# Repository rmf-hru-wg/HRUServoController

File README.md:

UEC RMF HRU Servo Controller Board RP2040
===

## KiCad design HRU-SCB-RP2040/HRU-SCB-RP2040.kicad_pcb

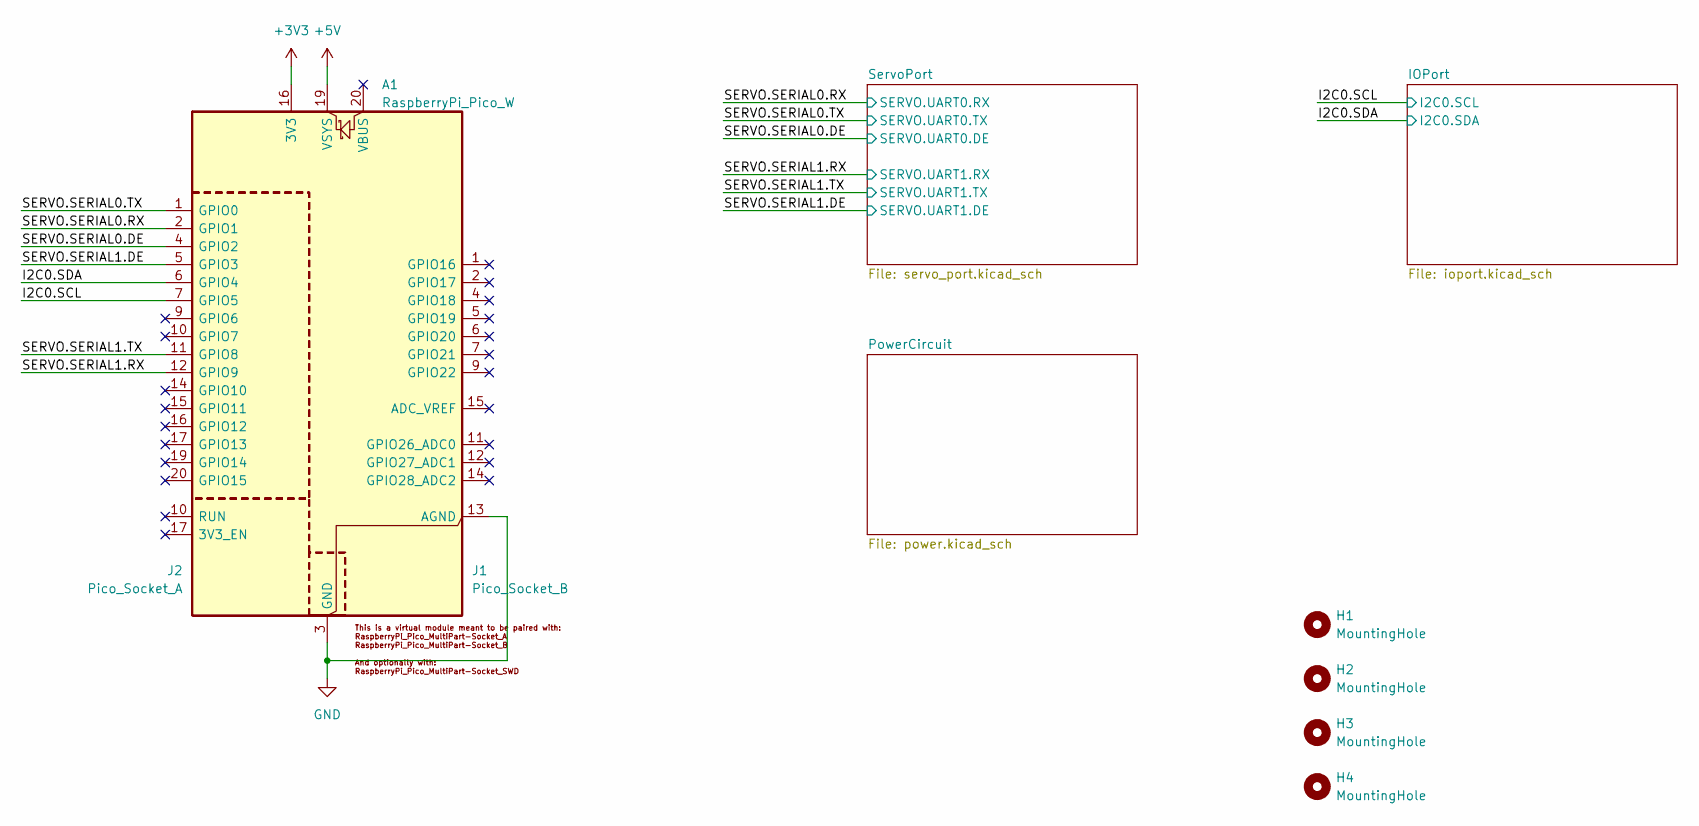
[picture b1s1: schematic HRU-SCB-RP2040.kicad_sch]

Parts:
A1: RaspberryPi_Pico_W; RaspberryPi_Pico_W_Virtual
H1, H2, H3, H4: MountingHole; MountingHole_3.2mm_M3
J1: Pico_Socket_B; RaspberryPi_Pico_PinSocket_1x20_P2.54mm_Vertical
J2: Pico_Socket_A; RaspberryPi_Pico_PinSocket_1x20_P2.54mm_Vertical

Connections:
+3V3: J1.16 (3V3); also elsewhere on the board
+5V: J1.19 (VSYS); also elsewhere on the board
/I2C0.SCL: J2.7 (GPIO5); also elsewhere on the board
/I2C0.SDA: J2.6 (GPIO4); also elsewhere on the board
/SERVO.SERIAL0.DE: J2.4 (GPIO2); also elsewhere on the board
/SERVO.SERIAL0.RX: J2.2 (GPIO1); also elsewhere on the board
/SERVO.SERIAL0.TX: J2.1 (GPIO0); also elsewhere on the board
/SERVO.SERIAL1.DE: J2.5 (GPIO3); also elsewhere on the board
/SERVO.SERIAL1.RX: J2.12 (GPIO9); also elsewhere on the board
/SERVO.SERIAL1.TX: J2.11 (GPIO8); also elsewhere on the board
GND: J1.3 (GND), J1.8 (GND), J1.13 (AGND), J1.18 (GND), J2.3 (GND), J2.8 (GND), J2.13 (GND), J2.18 (GND); also elsewhere on the board

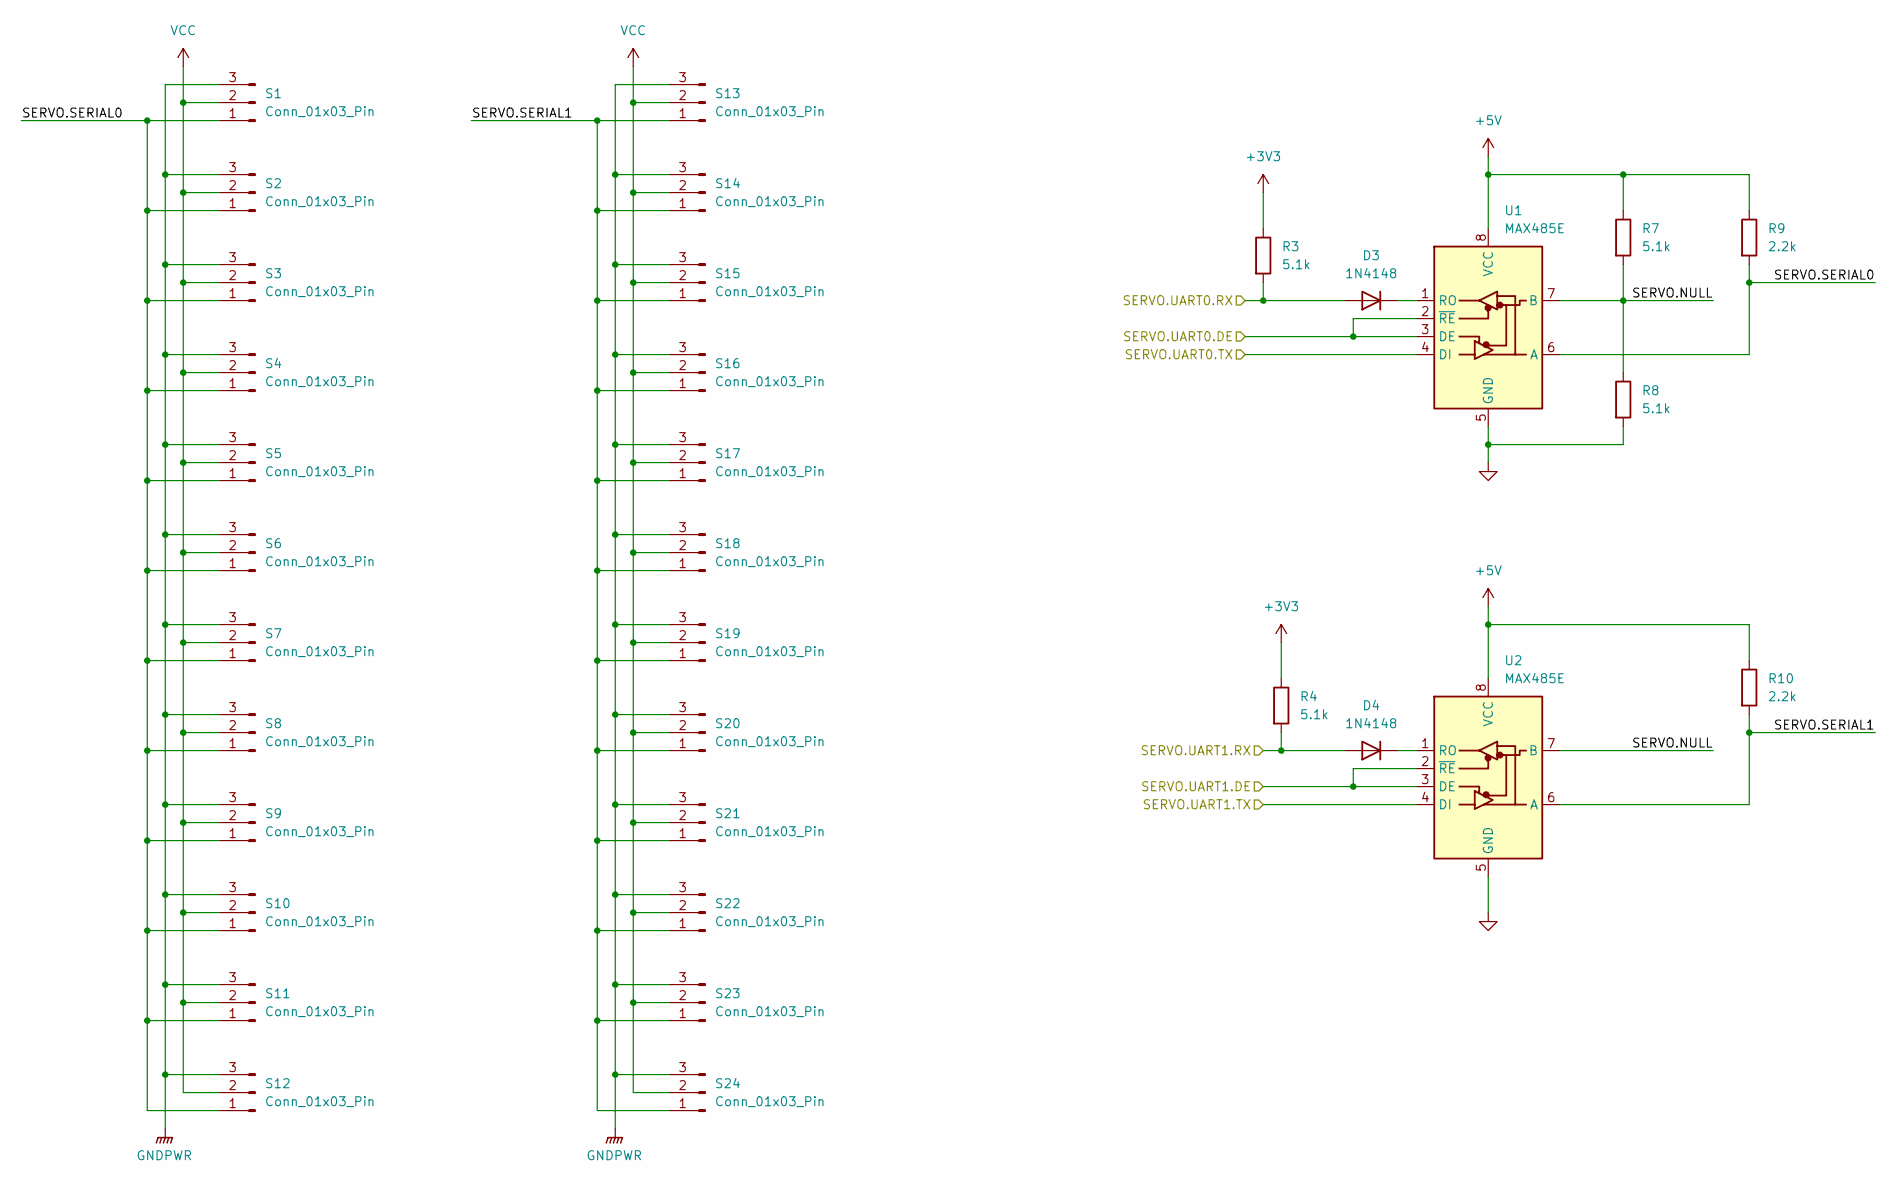
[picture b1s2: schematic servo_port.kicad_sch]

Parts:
D3, D4: 1N4148; D_T-1_P5.08mm_Horizontal
R3, R4, R7, R8: 5.1k; R_Axial_DIN0207_L6.3mm_D2.5mm_P7.62mm_Horizontal
R9, R10: 2.2k; R_Axial_DIN0207_L6.3mm_D2.5mm_P7.62mm_Horizontal
S1, S2, S3, S4, S5, S6, S7, S8, S9, S10, S11, S12, S13, S14, S15, S16, S17, S18, S19, S20, S21, S22, S23, S24: Conn_01x03_Pin; PinHeader_1x03_P2.54mm_Vertical_SmallCourtyard
U1, U2: MAX485E; DIP-8_W7.62mm_Socket

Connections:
+3V3: R3.1, R4.1; also elsewhere on the board
+5V: R7.1, R9.1, R10.1, U1.8 (VCC), U2.8 (VCC); also elsewhere on the board
/SERVO.SERIAL0.DE: U1.2 (~RE), U1.3 (DE); also elsewhere on the board
/SERVO.SERIAL0.RX: D3.2 (A), R3.2; also elsewhere on the board
/SERVO.SERIAL0.TX: U1.4 (DI); also elsewhere on the board
/SERVO.SERIAL1.DE: U2.2 (~RE), U2.3 (DE); also elsewhere on the board
/SERVO.SERIAL1.RX: D4.2 (A), R4.2; also elsewhere on the board
/SERVO.SERIAL1.TX: U2.4 (DI); also elsewhere on the board
/ServoPort/SERVO.NULL: R7.2, R8.1, U1.7 (B), U2.7 (B)
/ServoPort/SERVO.SERIAL0: R9.2, S1.1, S2.1, S3.1, S4.1, S5.1, S6.1, S7.1, S8.1, S9.1, S10.1, S11.1, S12.1, U1.6 (A)
/ServoPort/SERVO.SERIAL1: R10.2, S13.1, S14.1, S15.1, S16.1, S17.1, S18.1, S19.1, S20.1, S21.1, S22.1, S23.1, S24.1, U2.6 (A)
GND: R8.2, U1.5 (GND), U2.5 (GND); also elsewhere on the board
GNDPWR: S1.3, S2.3, S3.3, S4.3, S5.3, S6.3, S7.3, S8.3, S9.3, S10.3, S11.3, S12.3, S13.3, S14.3, S15.3, S16.3, S17.3, S18.3, S19.3, S20.3, S21.3, S22.3, S23.3, S24.3; also elsewhere on the board
unnamed: D3.1 (K), U1.1 (RO)
unnamed: D4.1 (K), U2.1 (RO)
VCC: S1.2, S2.2, S3.2, S4.2, S5.2, S6.2, S7.2, S8.2, S9.2, S10.2, S11.2, S12.2, S13.2, S14.2, S15.2, S16.2, S17.2, S18.2, S19.2, S20.2, S21.2, S22.2, S23.2, S24.2; also elsewhere on the board

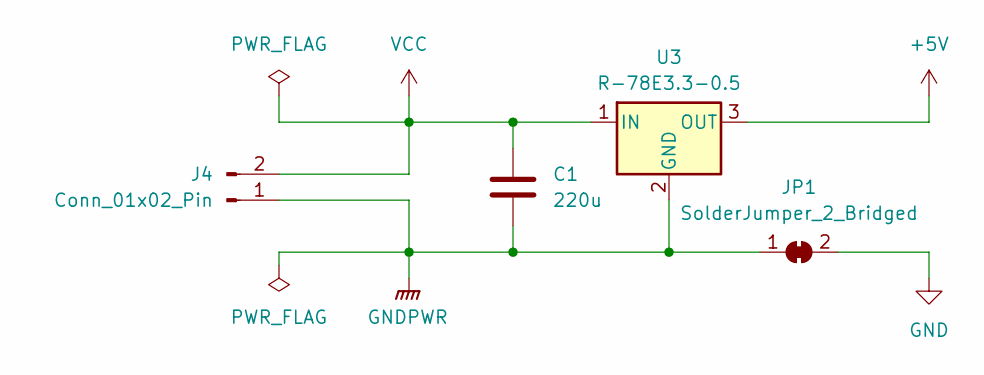
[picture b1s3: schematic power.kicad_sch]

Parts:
C1: 220u; C_Radial_D8.0mm_H11.5mm_P3.50mm
J4: Conn_01x02_Pin; AMASS_XT30UPB-M_1x02_P5.0mm_Vertical
JP1: SolderJumper_2_Bridged; SolderJumper-2_P1.3mm_Bridged_Pad1.0x1.5mm
U3: R-78E3.3-0.5; Converter_DCDC_RECOM_R-78E-0.5_THT

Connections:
+5V: U3.3 (OUT); also elsewhere on the board
GND: JP1.2 (B); also elsewhere on the board
GNDPWR: C1.2, J4.1, JP1.1 (A), U3.2 (GND); also elsewhere on the board
VCC: C1.1, J4.2, U3.1 (IN); also elsewhere on the board

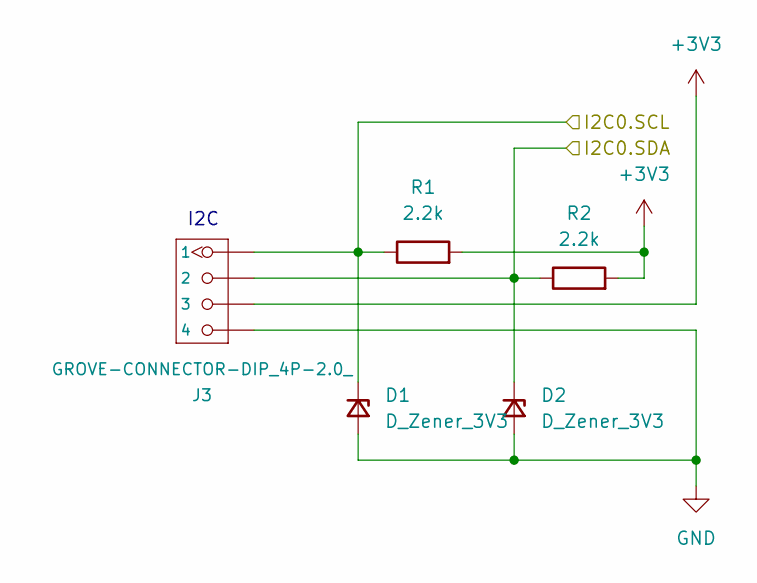
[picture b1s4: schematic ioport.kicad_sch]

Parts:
D1, D2: D_Zener_3V3; D_T-1_P5.08mm_Horizontal
J3: GROVE-CONNECTOR-DIP_4P-2.0_; GROVE-HW4-2.0
R1, R2: 2.2k; R_Axial_DIN0207_L6.3mm_D2.5mm_P7.62mm_Horizontal

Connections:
+3V3: J3.3, R1.2, R2.2; also elsewhere on the board
/I2C0.SCL: D1.1 (K), J3.1, R1.1; also elsewhere on the board
/I2C0.SDA: D2.1 (K), J3.2, R2.1; also elsewhere on the board
GND: D1.2 (A), D2.2 (A), J3.4; also elsewhere on the board

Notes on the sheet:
I2C

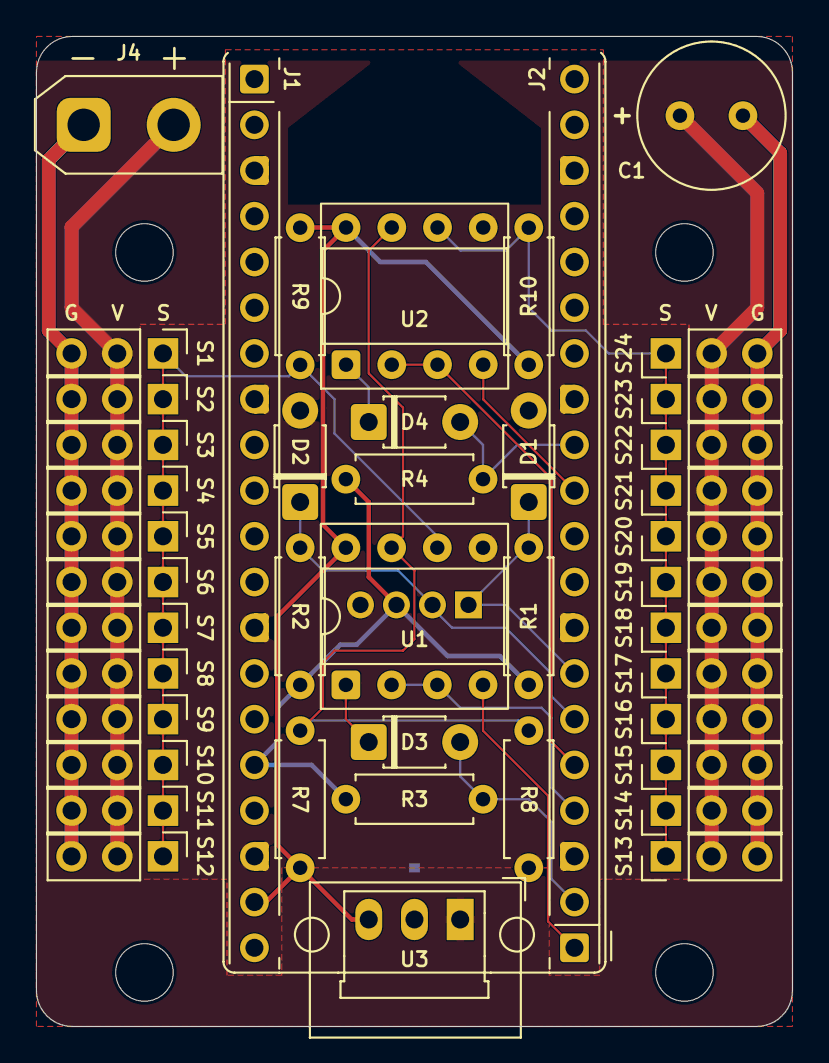
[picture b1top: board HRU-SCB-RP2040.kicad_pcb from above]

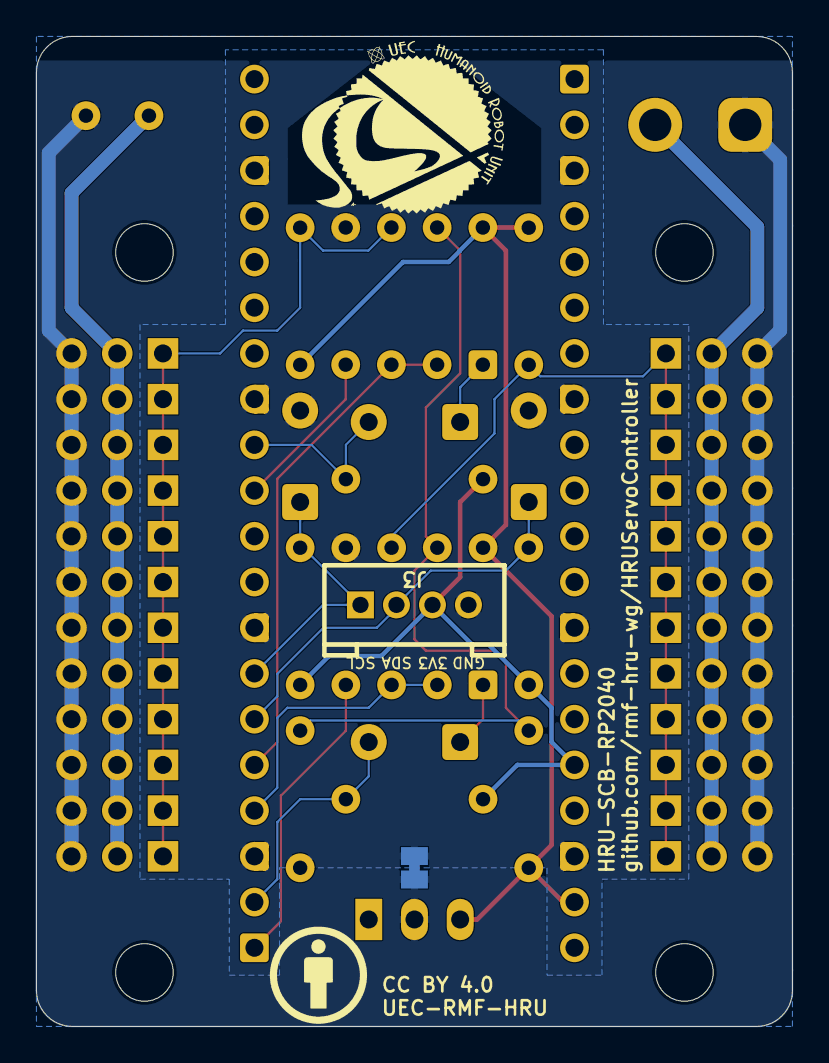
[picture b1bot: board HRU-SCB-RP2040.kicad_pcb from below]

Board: 2 copper layers, 42.0 x 55.0 mm, 50 parts (2 on the bottom side), 18 nets.

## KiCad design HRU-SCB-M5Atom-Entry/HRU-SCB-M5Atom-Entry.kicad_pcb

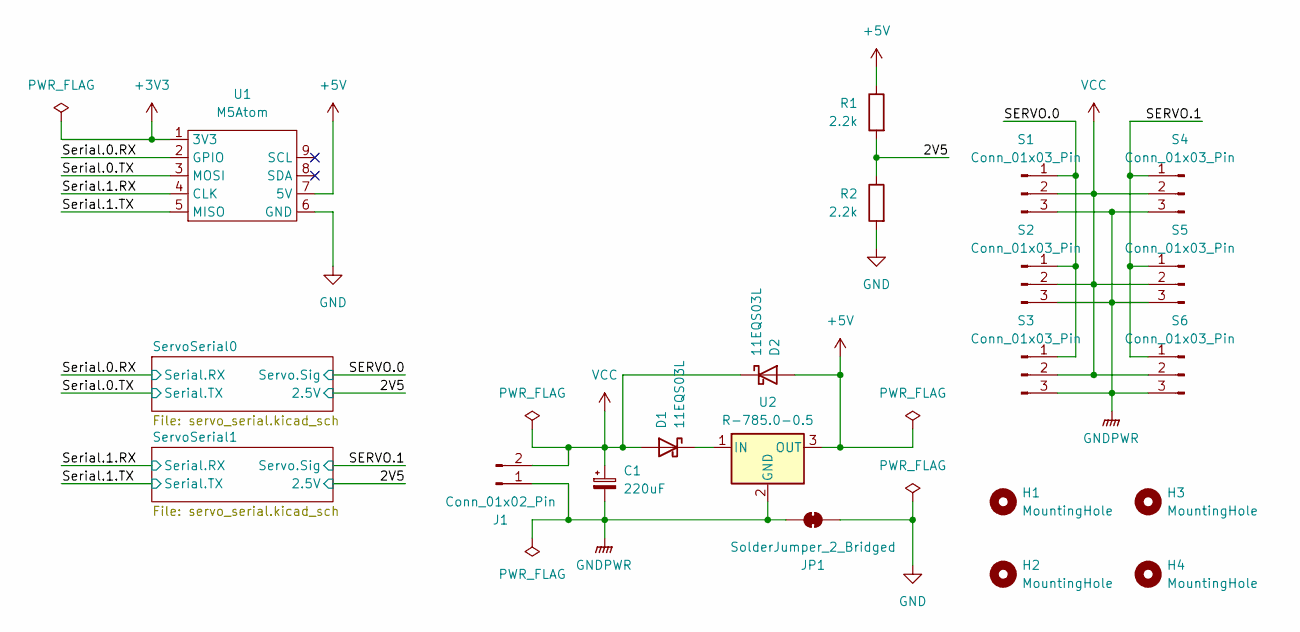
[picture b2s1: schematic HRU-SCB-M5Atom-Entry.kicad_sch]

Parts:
C1: 220uF; CP_Radial_D6.3mm_P2.50mm
D1, D2: 11EQS03L; D_T-1_P5.08mm_Horizontal
H1, H2, H3, H4: MountingHole; MountingHole_2.2mm_M2
J1: Conn_01x02_Pin; AMASS_XT30U-M_1x02_P5.0mm_Vertical
JP1: SolderJumper_2_Bridged; SolderJumper-2_P1.3mm_Bridged_Pad1.0x1.5mm
R1, R2: 2.2k; R_Axial_DIN0207_L6.3mm_D2.5mm_P7.62mm_Horizontal
S1, S2, S3, S4, S5, S6: Conn_01x03_Pin; PinHeader_1x03_P2.54mm_Vertical_SmallCourtyard
U1: M5Atom
U2: R-785.0-0.5; Converter_DCDC_RECOM_R-78E-0.5_THT

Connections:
+3V3: U1.1 (3V3); also elsewhere on the board
+5V: D2.2 (A), R1.1, U1.7 (5V), U2.3 (OUT); also elsewhere on the board
/2V5: R1.2, R2.1; also elsewhere on the board
/SERVO.0: S1.1, S2.1, S3.1; also elsewhere on the board
/SERVO.1: S4.1, S5.1, S6.1; also elsewhere on the board
/Serial.0.RX: U1.2 (GPIO); also elsewhere on the board
/Serial.0.TX: U1.3 (MOSI); also elsewhere on the board
/Serial.1.RX: U1.4 (CLK); also elsewhere on the board
/Serial.1.TX: U1.5 (MISO); also elsewhere on the board
GND: JP1.2 (B), R2.2, U1.6 (GND); also elsewhere on the board
GNDPWR: C1.2, J1.1, JP1.1 (A), S1.3, S2.3, S3.3, S4.3, S5.3, S6.3, U2.2 (GND)
unnamed: D1.1 (K), U2.1 (IN)
VCC: C1.1, D1.2 (A), D2.1 (K), J1.2, S1.2, S2.2, S3.2, S4.2, S5.2, S6.2

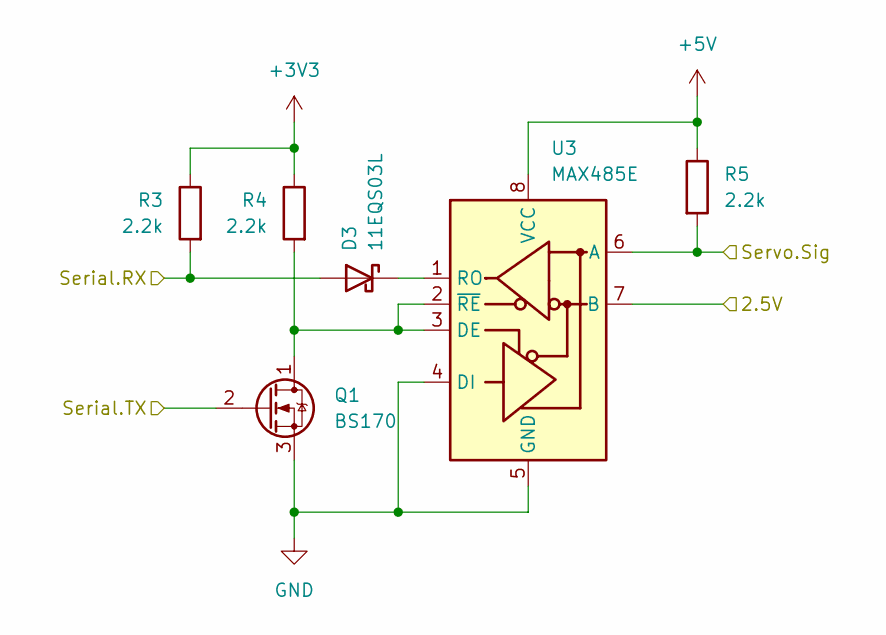
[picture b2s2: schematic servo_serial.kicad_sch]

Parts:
D3: 11EQS03L; D_T-1_P5.08mm_Horizontal
Q1: BS170; TO-92_Inline
R3, R4, R5: 2.2k; R_Axial_DIN0207_L6.3mm_D2.5mm_P7.62mm_Horizontal
U3: MAX485E; DIP-8_W7.62mm_Socket

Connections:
+3V3: R3.1, R4.1; also elsewhere on the board
+5V: R5.1, U3.8 (VCC); also elsewhere on the board
/2V5: U3.7 (B); also elsewhere on the board
/SERVO.0: R5.2, U3.6 (A); also elsewhere on the board
/Serial.0.RX: D3.2 (A), R3.2; also elsewhere on the board
/Serial.0.TX: Q1.2 (G); also elsewhere on the board
GND: Q1.3 (S), U3.4 (DI), U3.5 (GND); also elsewhere on the board
unnamed: D3.1 (K), U3.1 (RO)
unnamed: Q1.1 (D), R4.2, U3.2 (~RE), U3.3 (DE)

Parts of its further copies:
D4: 11EQS03L; D_T-1_P5.08mm_Horizontal
Q2: BS170; TO-92_Inline
R6, R7, R8: 2.2k; R_Axial_DIN0207_L6.3mm_D2.5mm_P7.62mm_Horizontal
U4: MAX485E; DIP-8_W7.62mm_Socket

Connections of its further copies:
+3V3: R6.1, R7.1; also elsewhere on the board
+5V: R8.1, U4.8 (VCC); also elsewhere on the board
/2V5: U4.7 (B); also elsewhere on the board
/SERVO.1: R8.2, U4.6 (A); also elsewhere on the board
/Serial.1.RX: D4.2 (A), R6.2; also elsewhere on the board
/Serial.1.TX: Q2.2 (G); also elsewhere on the board
GND: Q2.3 (S), U4.4 (DI), U4.5 (GND); also elsewhere on the board
unnamed: D4.1 (K), U4.1 (RO)
unnamed: Q2.1 (D), R7.2, U4.2 (~RE), U4.3 (DE)

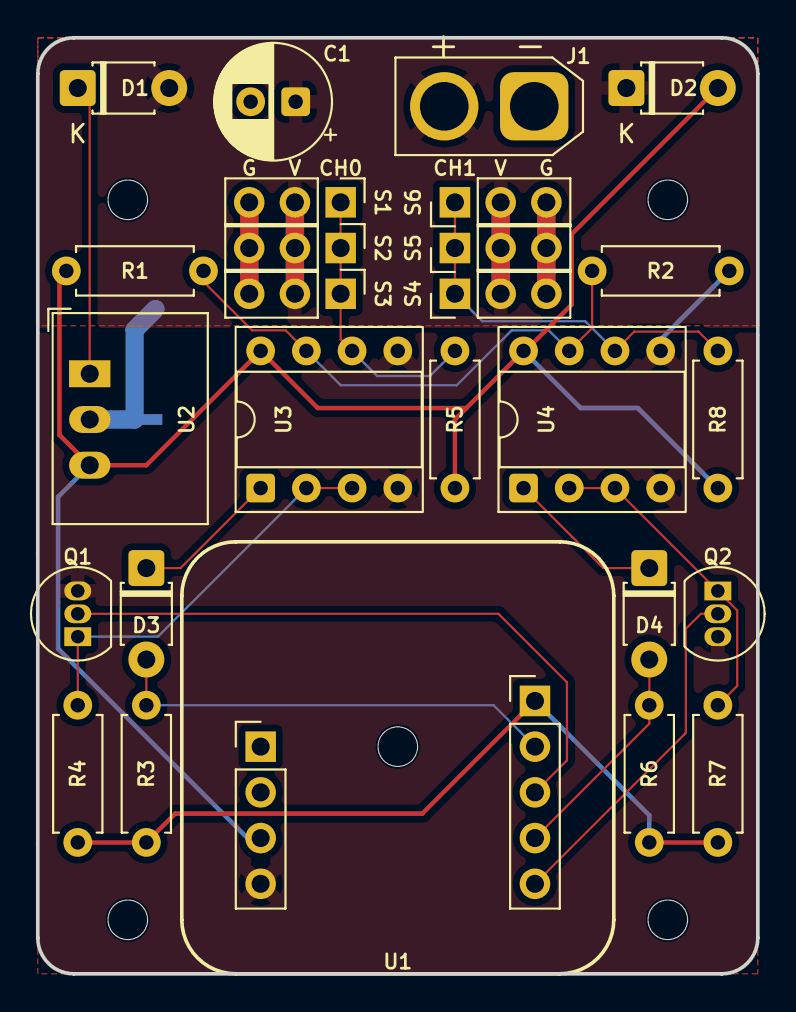
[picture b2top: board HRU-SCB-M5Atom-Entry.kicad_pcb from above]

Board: 2 copper layers, 40.0 x 52.0 mm, 31 parts (1 on the bottom side), 17 nets.

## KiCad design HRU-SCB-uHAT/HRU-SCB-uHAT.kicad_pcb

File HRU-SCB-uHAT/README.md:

# HRU-SCB-uHAT

## Tri-State

3.3VレベルのUARTからシリアルサーボ向けの5V半二重シリアルに変換するICの選定。
SC16IS762を使用するので、同系列からNexperiaの74系ロジックICより2G241のシリーズを選択。
最終的にTTLサポートで主電源5V前後での使用を想定した汎用ICから、74AHCT2G241とした。
<https://assets.nexperia.com/documents/data-sheet/74AHC_AHCT2G241.pdf>

なお74系はLVCやAHC/Tなどいくつかのシリーズがあるが、NexperiaのLogic Application Handbookにある"Table 6: Picogate portfolio Parametrics and features"などがわかりやすい。
<https://www.nexperia.com/dam/jcr:851f7c27-b0e9-4627-84b9-13b132388708/Nexperia_LOGIC_Handbook.pdf>

## Reference

- Raspberry Pi HAT Specification: https://github.com/raspberrypi/hats
- SC16IS752 Linux Driver: https://github.com/raspberrypi/linux/issues/3231

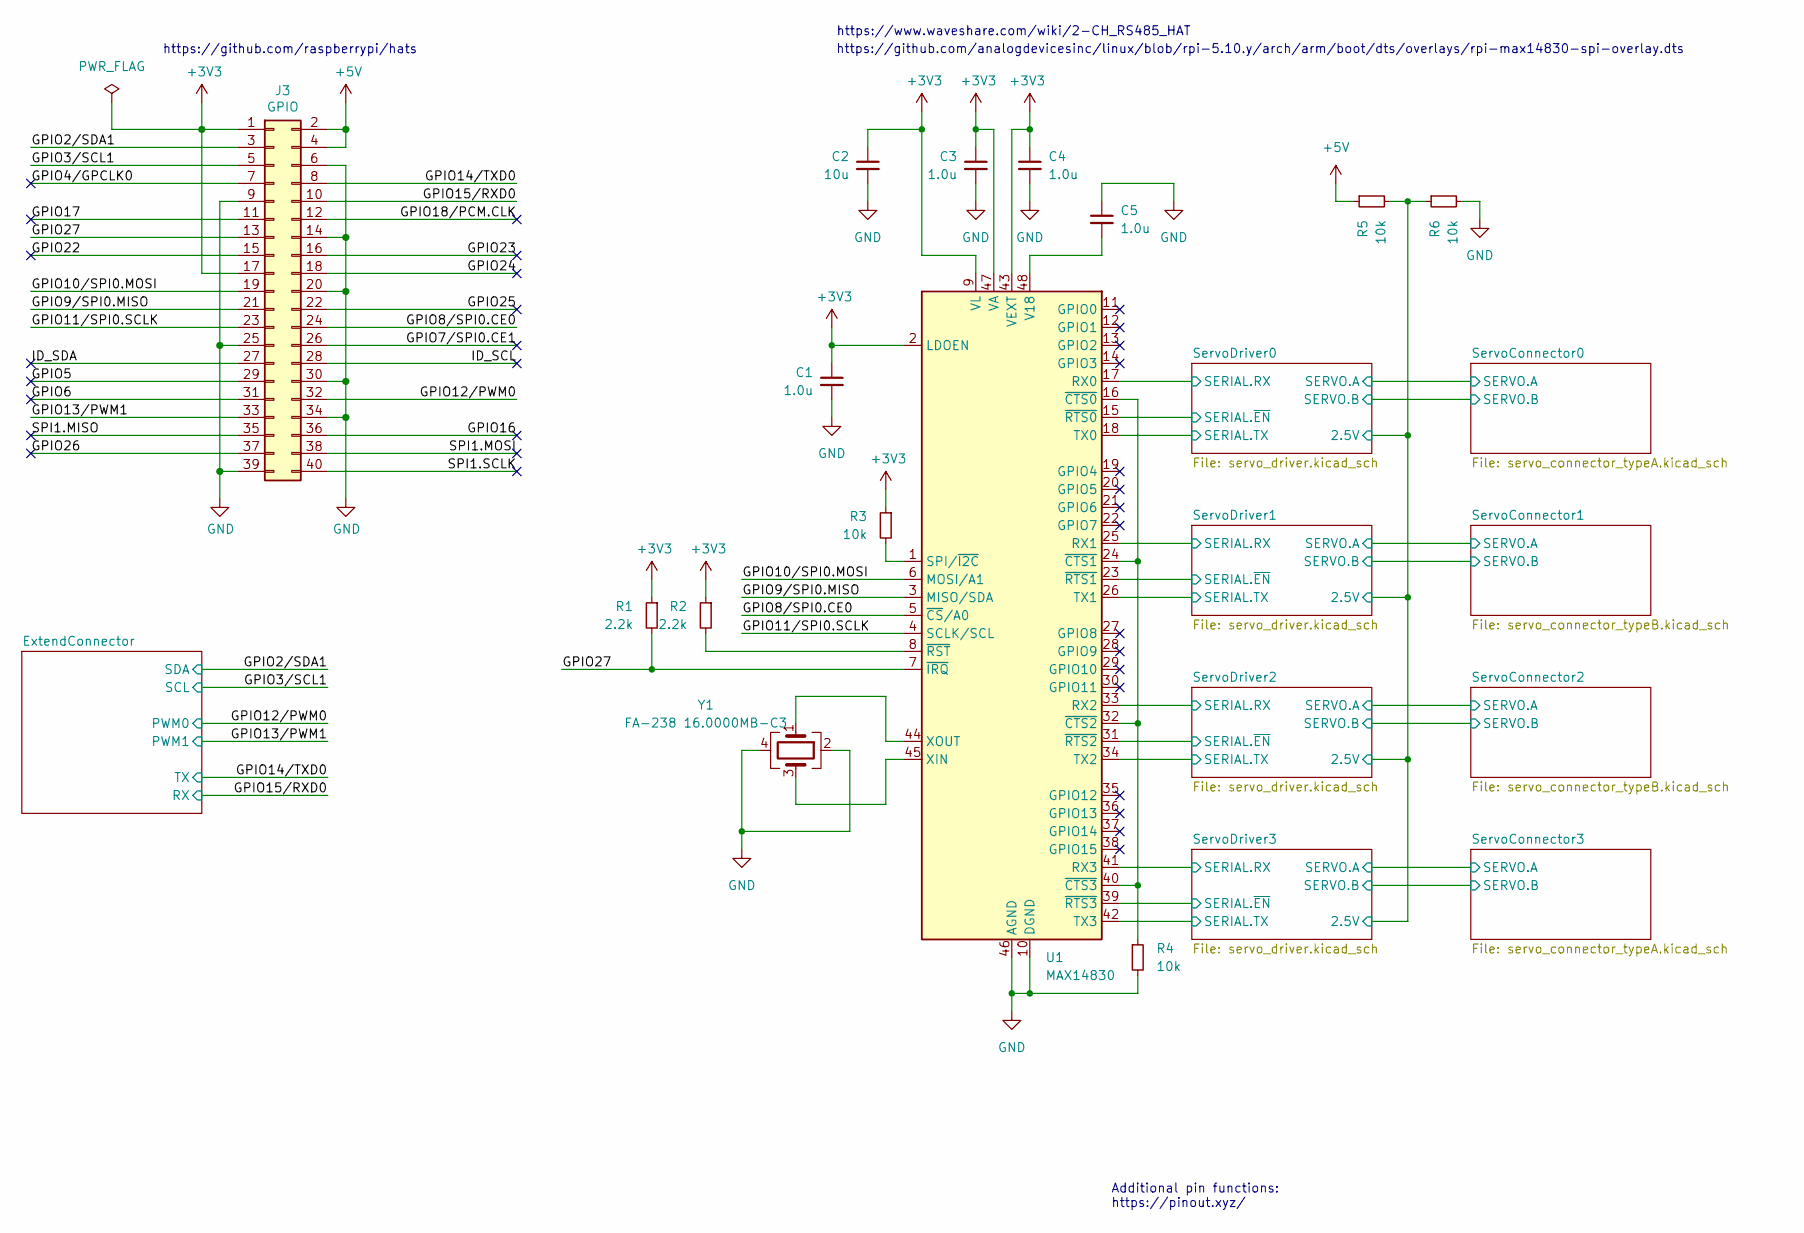
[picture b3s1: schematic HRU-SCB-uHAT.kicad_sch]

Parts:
C1, C3, C4, C5: 1.0u; C_0603_1608Metric_Pad1.08x0.95mm_HandSolder
C2: 10u; C_0603_1608Metric_Pad1.08x0.95mm_HandSolder
J3: GPIO; PinSocket_2x20_P2.54mm_Vertical_SMD
R1, R2: 2.2k; R_0603_1608Metric_Pad0.98x0.95mm_HandSolder
R3, R4, R5, R6: 10k; R_0603_1608Metric_Pad0.98x0.95mm_HandSolder
U1: MAX14830; TQFN-48-1EP_7x7mm_P0.5mm_EP5.1x5.1mm
Y1: FA-238 16.0000MB-C3; Crystal_SMD_3225-4Pin_3.2x2.5mm_HandSoldering

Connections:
+3V3: C1.1, C2.1, C3.1, C4.1, J3.1, J3.17, R1.1, R2.1, R3.1, U1.2 (LDOEN), U1.9 (VL), U1.43 (VEXT), U1.47 (VA); also elsewhere on the board
+5V: J3.2, J3.4, R5.1; also elsewhere on the board
/GPIO2/SDA1: J3.3; also elsewhere on the board
/GPIO3/SCL1: J3.5; also elsewhere on the board
/GPIO4/GPCLK0: J3.7
/GPIO5: J3.29
/GPIO6: J3.31
/GPIO7/SPI0.CE1: J3.26
/GPIO8/SPI0.CE0: J3.24, U1.5 (~CS/A0)
/GPIO9/SPI0.MISO: J3.21, U1.3 (MISO/SDA)
/GPIO10/SPI0.MOSI: J3.19, U1.6 (MOSI/A1)
/GPIO11/SPI0.SCLK: J3.23, U1.4 (SCLK/SCL)
/GPIO12/PWM0: J3.32; also elsewhere on the board
/GPIO13/PWM1: J3.33; also elsewhere on the board
/GPIO14/TXD0: J3.8; also elsewhere on the board
/GPIO15/RXD0: J3.10; also elsewhere on the board
/GPIO16: J3.36
/GPIO17: J3.11
/GPIO18/PCM.CLK: J3.12
/GPIO22: J3.15
/GPIO23: J3.16
/GPIO24: J3.18
/GPIO25: J3.22
/GPIO26: J3.37
/GPIO27: J3.13, R1.2, U1.7 (~IRQ)
/ID_SCL: J3.28
/ID_SDA: J3.27
/SPI1.MISO: J3.35
/SPI1.MOSI: J3.38
/SPI1.SCLK: J3.40
/ServoDriver0/2.5V: R5.2, R6.1; also elsewhere on the board
/ServoDriver0/SERIAL.RX: U1.17 (RX0); also elsewhere on the board
/ServoDriver0/SERIAL.TX: U1.18 (TX0); also elsewhere on the board
/ServoDriver0/SERIAL.~EN: U1.15 (~RTS0); also elsewhere on the board
/ServoDriver1/SERIAL.RX: U1.25 (RX1); also elsewhere on the board
/ServoDriver1/SERIAL.TX: U1.26 (TX1); also elsewhere on the board
/ServoDriver1/SERIAL.~EN: U1.23 (~RTS1); also elsewhere on the board
/ServoDriver2/SERIAL.RX: U1.33 (RX2); also elsewhere on the board
/ServoDriver2/SERIAL.TX: U1.34 (TX2); also elsewhere on the board
/ServoDriver2/SERIAL.~EN: U1.31 (~RTS2); also elsewhere on the board
/ServoDriver3/SERIAL.RX: U1.41 (RX3); also elsewhere on the board
/ServoDriver3/SERIAL.TX: U1.42 (TX3); also elsewhere on the board
/ServoDriver3/SERIAL.~EN: U1.39 (~RTS3); also elsewhere on the board
GND: C1.2, C2.2, C3.2, C4.2, C5.1, J3.6, J3.9, J3.14, J3.20, J3.25, J3.30, J3.34, J3.39, R4.2, R6.2, U1.10 (DGND), U1.46 (AGND), U1.49 (AGND), Y1.2, Y1.4; also elsewhere on the board
unnamed: R3.2, U1.1 (SPI/~I2C)
unnamed: C5.2, U1.48 (V18)
unnamed: U1.45 (XIN), Y1.3
unnamed: U1.44 (XOUT), Y1.1
unnamed: R4.1, U1.16 (~CTS0), U1.24 (~CTS1), U1.32 (~CTS2), U1.40 (~CTS3)
unnamed: R2.2, U1.8 (~RST)

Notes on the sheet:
https://github.com/analogdevicesinc/linux/blob/rpi-5.10.y/arch/arm/boot/dts/overlays/rpi-max14830-spi-overlay.dts
https://www.waveshare.com/wiki/2-CH_RS485_HAT
https://github.com/raspberrypi/hats
Additional pin functions: https://pinout.xyz/

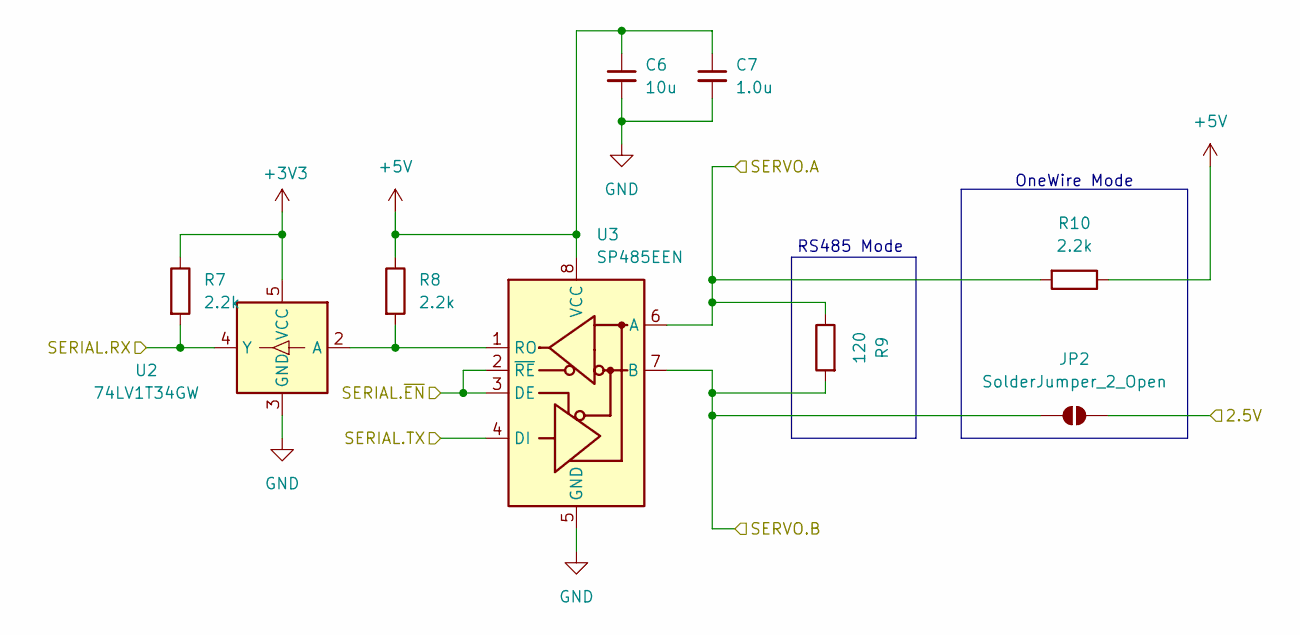
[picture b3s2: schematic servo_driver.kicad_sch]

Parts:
C6: 10u; C_0603_1608Metric_Pad1.08x0.95mm_HandSolder
C7: 1.0u; C_0603_1608Metric_Pad1.08x0.95mm_HandSolder
JP2: SolderJumper_2_Open; SolderJumper-2_P1.3mm_Open_TrianglePad1.0x1.5mm
R7, R8, R10: 2.2k; R_0603_1608Metric_Pad0.98x0.95mm_HandSolder
R9: 120; R_0603_1608Metric_Pad0.98x0.95mm_HandSolder
U2: 74LV1T34GW; SOT-353_SC-70-5
U3: SP485EEN; SOIC-8_3.9x4.9mm_P1.27mm

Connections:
+3V3: R7.1, U2.5 (VCC); also elsewhere on the board
+5V: C6.1, C7.1, R8.1, R10.1, U3.8 (VCC); also elsewhere on the board
/ServoConnector0/SERVO.A: R9.1, R10.2, U3.6 (A); also elsewhere on the board
/ServoConnector0/SERVO.B: JP2.1 (A), R9.2, U3.7 (B); also elsewhere on the board
/ServoDriver0/2.5V: JP2.2 (B); also elsewhere on the board
/ServoDriver0/SERIAL.RX: R7.2, U2.4 (Y); also elsewhere on the board
/ServoDriver0/SERIAL.TX: U3.4 (DI); also elsewhere on the board
/ServoDriver0/SERIAL.~EN: U3.2 (~RE), U3.3 (DE); also elsewhere on the board
GND: C6.2, C7.2, U2.3 (GND), U3.5 (GND); also elsewhere on the board
unnamed: R8.2, U2.2 (A), U3.1 (RO)

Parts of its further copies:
C8, C10, C12: 10u; C_0603_1608Metric_Pad1.08x0.95mm_HandSolder
C9, C11, C13: 1.0u; C_0603_1608Metric_Pad1.08x0.95mm_HandSolder
JP3, JP4, JP5: SolderJumper_2_Open; SolderJumper-2_P1.3mm_Open_TrianglePad1.0x1.5mm
R11, R12, R14, R15, R16, R18, R19, R20, R22: 2.2k; R_0603_1608Metric_Pad0.98x0.95mm_HandSolder
R13, R17, R21: 120; R_0603_1608Metric_Pad0.98x0.95mm_HandSolder
U4, U6, U8: 74LV1T34GW; SOT-353_SC-70-5
U5, U7, U9: SP485EEN; SOIC-8_3.9x4.9mm_P1.27mm

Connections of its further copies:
+3V3: R11.1, R15.1, R19.1, U4.5 (VCC), U6.5 (VCC), U8.5 (VCC); also elsewhere on the board
+5V: C8.1, C9.1, C10.1, C11.1, C12.1, C13.1, R12.1, R14.1, R16.1, R18.1, R20.1, R22.1, U5.8 (VCC), U7.8 (VCC), U9.8 (VCC); also elsewhere on the board
/ServoConnector1/SERVO.A: R13.1, R14.2, U5.6 (A); also elsewhere on the board
/ServoConnector1/SERVO.B: JP3.1 (A), R13.2, U5.7 (B); also elsewhere on the board
/ServoConnector2/SERVO.A: R17.1, R18.2, U7.6 (A); also elsewhere on the board
/ServoConnector2/SERVO.B: JP4.1 (A), R17.2, U7.7 (B); also elsewhere on the board
/ServoConnector3/SERVO.A: R21.1, R22.2, U9.6 (A); also elsewhere on the board
/ServoConnector3/SERVO.B: JP5.1 (A), R21.2, U9.7 (B); also elsewhere on the board
/ServoDriver0/2.5V: JP3.2 (B), JP4.2 (B), JP5.2 (B); also elsewhere on the board
/ServoDriver1/SERIAL.RX: R11.2, U4.4 (Y); also elsewhere on the board
/ServoDriver1/SERIAL.TX: U5.4 (DI); also elsewhere on the board
/ServoDriver1/SERIAL.~EN: U5.2 (~RE), U5.3 (DE); also elsewhere on the board
/ServoDriver2/SERIAL.RX: R15.2, U6.4 (Y); also elsewhere on the board
/ServoDriver2/SERIAL.TX: U7.4 (DI); also elsewhere on the board
/ServoDriver2/SERIAL.~EN: U7.2 (~RE), U7.3 (DE); also elsewhere on the board
/ServoDriver3/SERIAL.RX: R19.2, U8.4 (Y); also elsewhere on the board
/ServoDriver3/SERIAL.TX: U9.4 (DI); also elsewhere on the board
/ServoDriver3/SERIAL.~EN: U9.2 (~RE), U9.3 (DE); also elsewhere on the board
GND: C8.2, C9.2, C10.2, C11.2, C12.2, C13.2, U4.3 (GND), U5.5 (GND), U6.3 (GND), U7.5 (GND), U8.3 (GND), U9.5 (GND); also elsewhere on the board
unnamed: R12.2, U4.2 (A), U5.1 (RO)
unnamed: R16.2, U6.2 (A), U7.1 (RO)
unnamed: R20.2, U8.2 (A), U9.1 (RO)

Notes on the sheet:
RS485 Mode
OneWire Mode

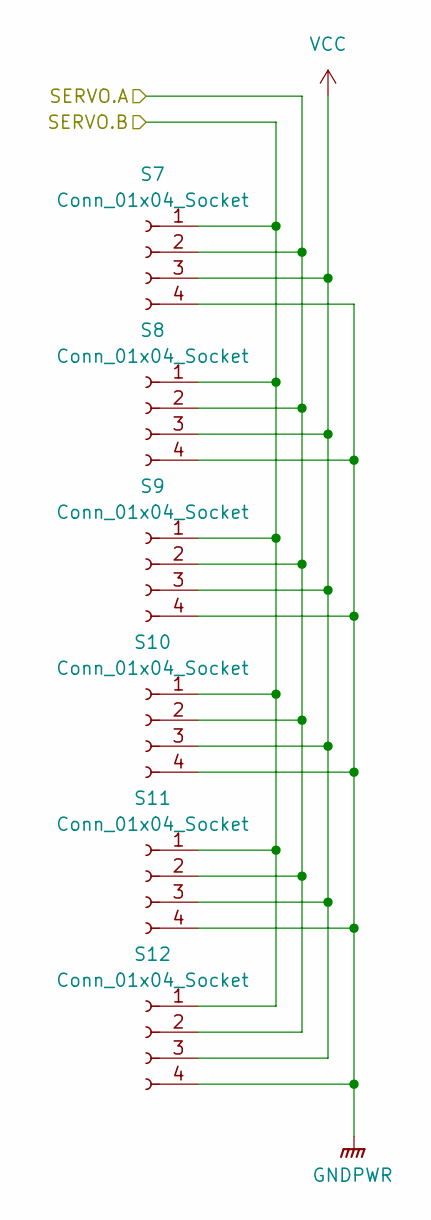
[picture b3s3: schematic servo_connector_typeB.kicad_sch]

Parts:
S7, S9, S11: Conn_01x04_Socket; PinHeader_1x04_P2.54mm_Vertical
S8, S10, S12: Conn_01x04_Socket; JST_EH_B4B-EH-A_1x04_P2.50mm_Vertical

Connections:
/ServoConnector1/SERVO.A: S7.2, S8.2, S9.2, S10.2, S11.2, S12.2; also elsewhere on the board
/ServoConnector1/SERVO.B: S7.1, S8.1, S9.1, S10.1, S11.1, S12.1; also elsewhere on the board
GNDPWR: S7.4, S8.4, S9.4, S10.4, S11.4, S12.4; also elsewhere on the board
VCC: S7.3, S8.3, S9.3, S10.3, S11.3, S12.3; also elsewhere on the board

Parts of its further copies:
S13, S15, S17: Conn_01x04_Socket; PinHeader_1x04_P2.54mm_Vertical
S14, S16, S18: Conn_01x04_Socket; JST_EH_B4B-EH-A_1x04_P2.50mm_Vertical

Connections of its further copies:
/ServoConnector2/SERVO.A: S13.2, S14.2, S15.2, S16.2, S17.2, S18.2; also elsewhere on the board
/ServoConnector2/SERVO.B: S13.1, S14.1, S15.1, S16.1, S17.1, S18.1; also elsewhere on the board
GNDPWR: S13.4, S14.4, S15.4, S16.4, S17.4, S18.4; also elsewhere on the board
VCC: S13.3, S14.3, S15.3, S16.3, S17.3, S18.3; also elsewhere on the board

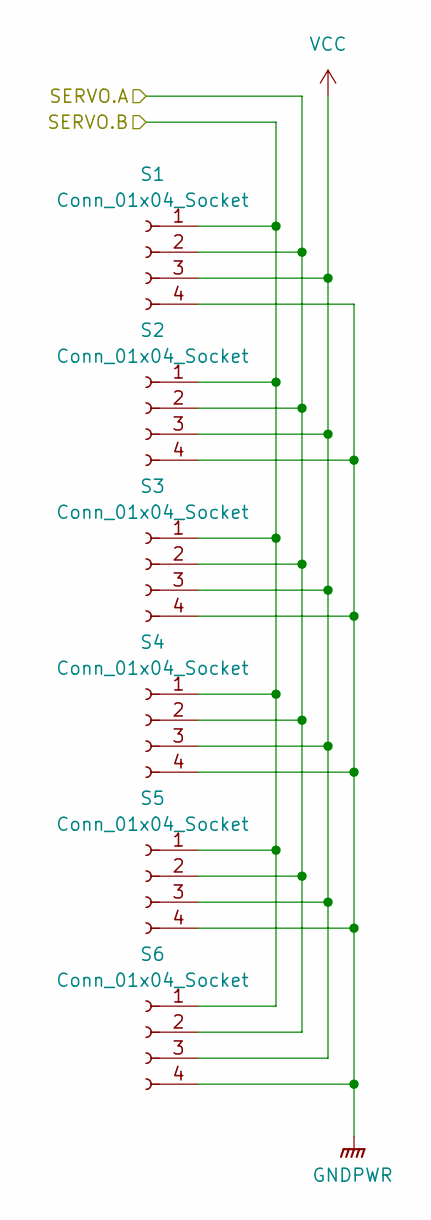
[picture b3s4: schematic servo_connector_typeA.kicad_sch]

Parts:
S1, S3, S5: Conn_01x04_Socket; JST_EH_B4B-EH-A_1x04_P2.50mm_Vertical
S2, S4, S6: Conn_01x04_Socket; PinHeader_1x04_P2.54mm_Vertical

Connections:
/ServoConnector0/SERVO.A: S1.2, S2.2, S3.2, S4.2, S5.2, S6.2; also elsewhere on the board
/ServoConnector0/SERVO.B: S1.1, S2.1, S3.1, S4.1, S5.1, S6.1; also elsewhere on the board
GNDPWR: S1.4, S2.4, S3.4, S4.4, S5.4, S6.4; also elsewhere on the board
VCC: S1.3, S2.3, S3.3, S4.3, S5.3, S6.3; also elsewhere on the board

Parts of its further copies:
S19, S21, S23: Conn_01x04_Socket; JST_EH_B4B-EH-A_1x04_P2.50mm_Vertical
S20, S22, S24: Conn_01x04_Socket; PinHeader_1x04_P2.54mm_Vertical

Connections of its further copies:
/ServoConnector3/SERVO.A: S19.2, S20.2, S21.2, S22.2, S23.2, S24.2; also elsewhere on the board
/ServoConnector3/SERVO.B: S19.1, S20.1, S21.1, S22.1, S23.1, S24.1; also elsewhere on the board
GNDPWR: S19.4, S20.4, S21.4, S22.4, S23.4, S24.4; also elsewhere on the board
VCC: S19.3, S20.3, S21.3, S22.3, S23.3, S24.3; also elsewhere on the board

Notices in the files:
HRU-SCB-M5Atom-Entry/HRU-SCB-M5Atom-Entry.kicad_pcb:
CC BY 4.0
